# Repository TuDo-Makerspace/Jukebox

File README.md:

# Jukebox

This repository contains everything related to our sacred Jukebox. For more information, please refer to one of the following sections:

- [Usage](https://tudo-makerspace.github.io/Jukebox/Docs/Usage.html)
- [Hardware Documentation](https://tudo-makerspace.github.io/Jukebox/Docs/Hardware.html)
- [Software Documentation]() TODO

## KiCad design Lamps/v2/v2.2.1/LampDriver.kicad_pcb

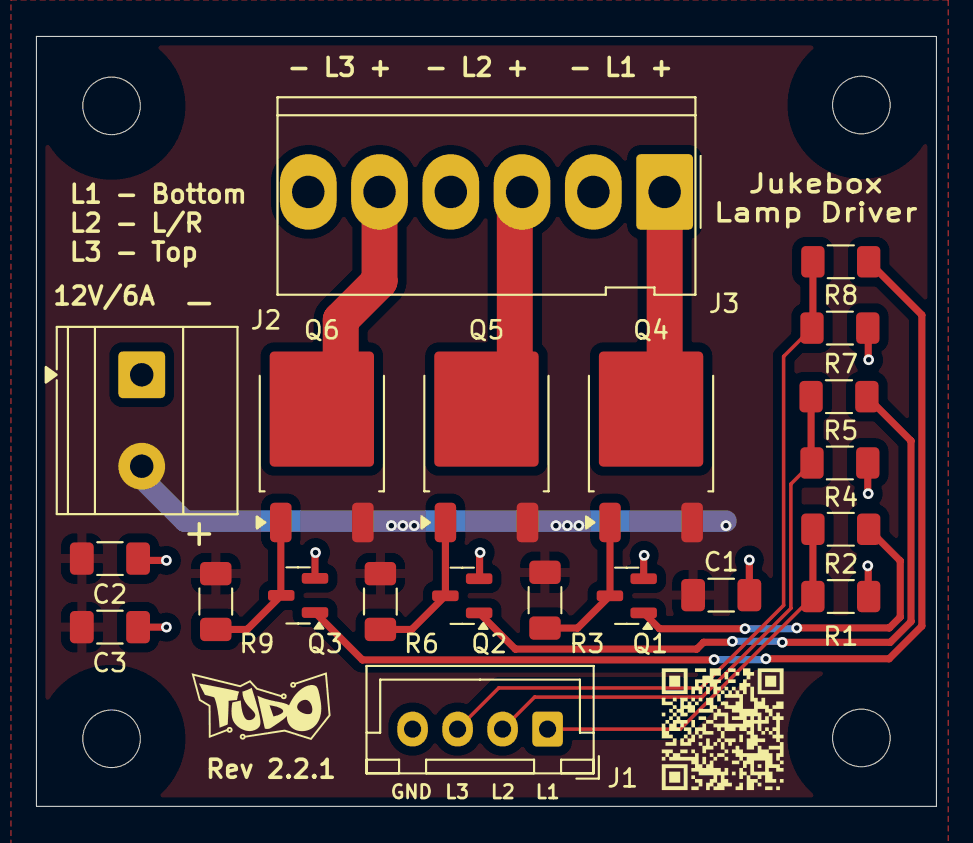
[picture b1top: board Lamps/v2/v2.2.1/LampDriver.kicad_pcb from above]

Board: 2 copper layers, 50.0 x 42.8 mm, 25 parts (0 on the bottom side), 14 nets.

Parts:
C1, C2: 100n; C_1206_3216Metric_Pad1.33x1.80mm_HandSolder
C3: 4.7u; C_1206_3216Metric_Pad1.33x1.80mm_HandSolder
H1, H2, H3, H4: MountingHole; MountingHole_3.2mm_M3
J1: JST XH 1x4; JST_XH_B4B-XH-A_1x04_P2.50mm_Vertical
J2: Screw_Terminal_01x02; TerminalBlock_Phoenix_MKDS-1,5-2-5.08_1x02_P5.08mm_Horizont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
J3: 1x6 MOLEX KK 396; Molex_KK-396_5273-06A_1x06_P3.96mm_Vertical
Q1, Q2, Q3: BSS138; SOT-23
Q4, Q5, Q6: FDD4141; TO-252-2
R1, R4, R7: 100k; R_1206_3216Metric_Pad1.30x1.75mm_HandSolder
R2, R5, R8: 470; R_1206_3216Metric_Pad1.30x1.75mm_HandSolder
R3, R6, R9: 47k; R_1206_3216Metric_Pad1.30x1.75mm_HandSolder

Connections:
+12V: C1.1, C2.1, C3.1, J2.2, Q4.3 (S), Q5.3 (S), Q6.3 (S), R3.1, R6.1, R9.1
/L1+: J3.1, Q4.2 (D)
/L2+: J3.3, Q5.2 (D)
/L3+: J3.5, Q6.2 (D)
GND: C1.2, C2.2, C3.2, J1.4, J2.1, J3.2, J3.4, J3.6, Q1.2 (S), Q2.2 (S), Q3.2 (S), R1.2, R4.2, R7.2
unnamed: J1.1, R1.1, R2.2
unnamed: J1.2, R4.1, R5.2
unnamed: J1.3, R7.1, R8.2
unnamed: Q1.3 (D), Q4.1 (G), R3.2
unnamed: Q1.1 (G), R2.1
unnamed: Q2.3 (D), Q5.1 (G), R6.2
unnamed: Q2.1 (G), R5.1
unnamed: Q3.3 (D), Q6.1 (G), R9.2
unnamed: Q3.1 (G), R8.1

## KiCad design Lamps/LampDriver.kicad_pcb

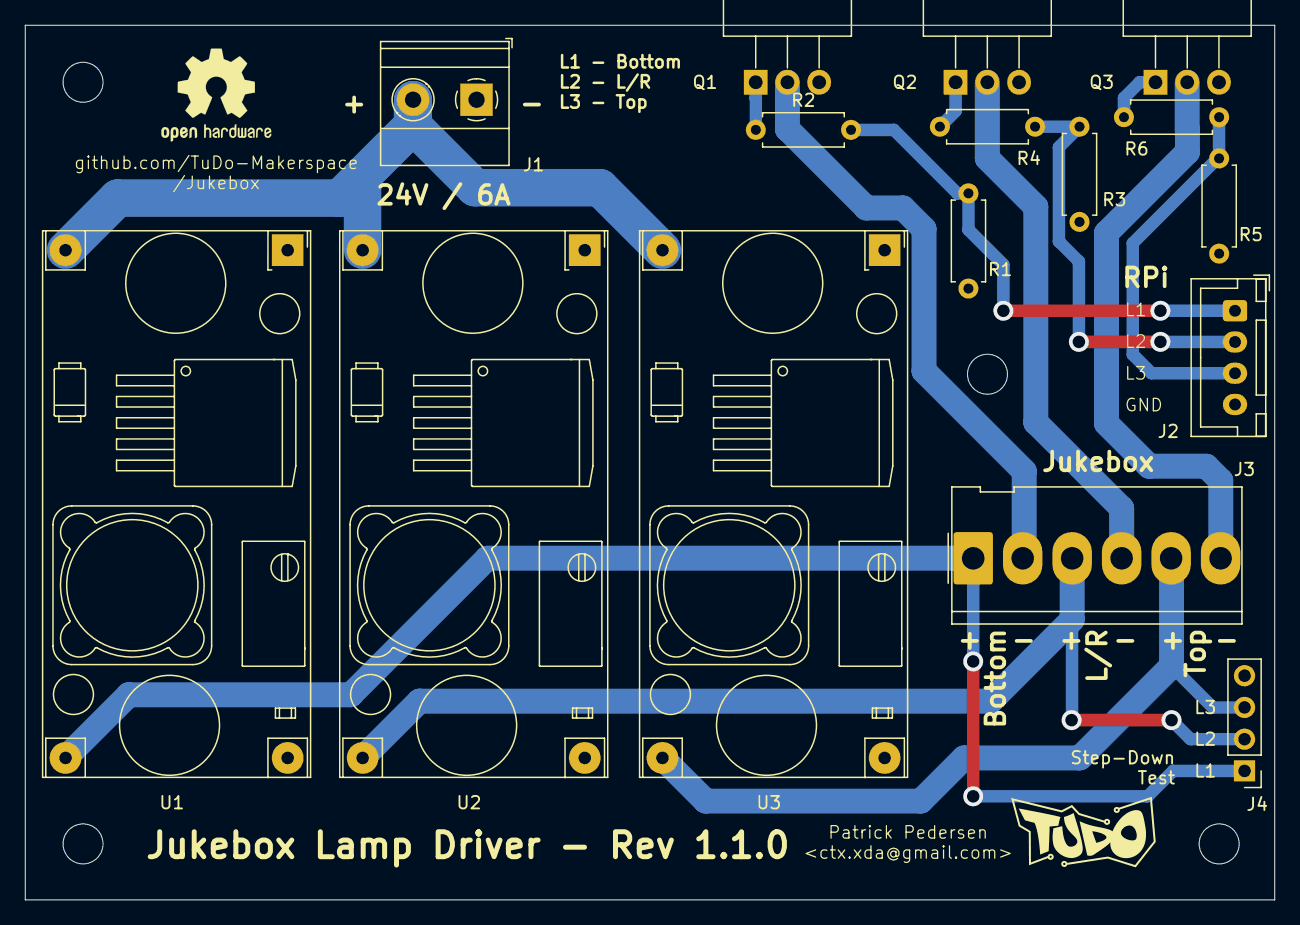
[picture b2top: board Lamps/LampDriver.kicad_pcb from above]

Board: 2 copper layers, 100.0 x 70.0 mm, 20 parts (0 on the bottom side), 14 nets.

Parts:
H1, H2, H3, H4: MountingHole; MountingHole_3.2mm_M3
J1: Screw_Terminal_01x02; TerminalBlock_Phoenix_MKDS-1,5-2-5.08_1x02_P5.08mm_Horizont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
J2: JST XH 1x4; JST_XH_B4B-XH-A_1x04_P2.50mm_Vertical
J3: Conn_01x06; Molex_KK-396_5273-06A_1x06_P3.96mm_Vertical
J4: Conn_01x04; PinHeader_1x04_P2.54mm_Vertical
Q1, Q2, Q3: IRFZ44N; TO-220-3_Horizontal_TabDown
R1, R3, R5: 100k; R_Axial_DIN0207_L6.3mm_D2.5mm_P7.62mm_Horizontal
R2, R4, R6: 470; R_Axial_DIN0207_L6.3mm_D2.5mm_P7.62mm_Horizontal
U1, U2, U3: DCDC_StepDown_LM2596; YAAJ_DCDC_StepDown_LM2596_Foxed

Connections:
+24V: J1.2, U1.1 (Vin), U2.1 (Vin), U3.1 (Vin)
/L1+: J3.1, J4.1, U1.4 (Vout)
/L1-: J3.2, Q1.2 (D)
/L2+: J3.3, J4.2, U2.4 (Vout)
/L2-: J3.4, Q2.2 (D)
/L3+: J3.5, J4.3, U3.4 (Vout)
/L3-: J3.6, Q3.2 (D)
GND: J1.1, J2.4, J4.4, Q1.3 (S), Q2.3 (S), Q3.3 (S), R1.2, R3.2, R5.2, U1.2 (GND), U1.3 (GND), U2.2 (GND), U2.3 (GND), U3.2 (GND), U3.3 (GND)
unnamed: J2.1, R1.1, R2.2
unnamed: J2.2, R3.1, R4.2
unnamed: J2.3, R5.1, R6.2
unnamed: Q1.1 (G), R2.1
unnamed: Q2.1 (G), R4.1
unnamed: Q3.1 (G), R6.1

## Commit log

2024-10-16 Added Lamp driver board
2024-10-16 Added adapter for speakers
2024-11-09 Added jukebox.py
2024-11-09 Added crude webserver to upload songs
2024-11-09 jukebox.py: Added play param to test playing
2024-11-09 Jukebox Webserver: Better upload errors + Fixed search bar
2024-11-10 Webserver: Added YouTube link support
2024-11-10 Webserver: Added spotify support
2024-11-10 Webserver: Expanded yt-dlp to more than just youtube links
2024-11-10 Webserver: Fixed upload buttons on phones
2024-11-10 Webserver: Added option to delte songs
2024-11-10 Webserver: Fixed uploads + BPM Tag after upload to reduce workload on jukebox.py
2024-11-10 Webserver: Added dark mode
2024-11-12 Renamed RPi/ to Software/
2024-11-12 Webserver: Run on port 80
2024-11-12 Software Setup: Added warning regarding missing assets
2024-11-12 Software Setup: Wait for services to activate
2024-11-12 Setup: Drop service check
2024-11-12 Jukebox: Keypad LUT
2024-11-12 Jukebox: Keypad mapping + Minor test arg fix
2024-11-12 Jukebox: Fixed keypad edgecase
2024-11-12 Jukebox: Added keypad timeout
2024-11-12 Webserver: Use env path!
2024-11-12 Removed accidental push of song
2024-11-12 Setup: Do not spam /etc/environment
2024-11-12 Jukebox: Play Track Not Found sample
2024-11-13 Jukebox: Added stop button + Other minor fixes
2024-11-13 Jukebox: Added boot light animation
2024-11-13 Jukebox: Added bpm multiplier to spice up the lights
2024-11-13 Jukebox: Added logs
2024-11-13 Jukebox: Dropped -p in favor of requiring JUKEBOX_SONGS_PATH
2024-11-14 Webserver: Outsource downloads to server if possible
2024-11-14 Webserver: Fixed white text on darkmode
2024-11-14 Setup: Add prompts for webserver env vars
2024-11-14 Webserver: Re-added -d
2024-11-14 Webserver: Fixed python formatting errors
2024-11-14 Fixed bad env vars
2024-11-14 Webserver: Added name feature + Better escaping
2024-11-14 Webserver: Added reminder to update title cards
2024-11-14 Webserver: Fixed Spotify Downloads
2024-11-14 Setup: Do not use -p in systemd service!
2024-11-14 Jukebox: Added support for random button
2024-11-14 Webserver: SSH: Disable StrictHostKeyChecking
2024-11-14 Jukebox: Fixed wrong compare on random button
2024-11-14 Webserver: Sanitize names because of @MarcelLeonMrgic :)
2024-11-14 Webserver: Break on characters in trackname
2024-11-14 Webserver: Limit track title in upload modal
2024-11-15 Jukebox: Implemented idle mode
2024-11-15 Jukebox: Minor fixes to idle mode
2024-11-15 Jukebox: More idle fixes
2024-11-15 Webserver: Allow 0-999
2024-11-15 Webserver: Fixed off-by-one error
2024-11-15 Jukebox: Added soundboard support
2024-11-16 Jukebox: Added soundboard
2024-11-16 Jukebox: Added function to set all lights
2024-11-16 Jukebox: Added timeout for soundboard mode
2024-11-16 Webserver: Added site for soundboard
2024-11-16 Webserver: Seperated css + Listen for ENTER in search bar
2024-11-17 Jukebox: Support soumdboard samples for non-numeric keys
2024-11-17 Webserver: Soundboard: Added support for R, G, RED and BLUE keys
2024-11-17 Jukebox: Soundboard: Added missing sample sound + Preload samples whenever we enter soundboard
2024-11-17 Webserver: Show reminder to re-enter soundboard after updating it
2024-11-17 Jukebox: If no command provided, show help
2024-11-17 Jukebox: Preload all assets to faster responsiveness
2024-11-18 Webserver: Show blue and red circle emojis for blue and red button in sb
2024-11-18 Jukebox: Sampling rate weirdness
2024-11-18 Jukebox: Sample buttons for better reliability + Fixed soundboard
2024-11-18 Jukebox: Renamed TrackNotFound.wav to TrackMissing.wav
2024-11-18 Added gitignore
2024-11-18 Jukebox: Soundboard: Play sample on button press, not release
2024-11-20 Webserver: See commit details
    Samples:
    - Fixed deletions of samples
    - Convert non 44100 or 48000 wavs to 44100
    As well as minor code clean-up
2024-11-20 Jukebox: Minor fixes
2024-11-20 Jukebox: Refactored key releasing
2024-11-20 Jukebox: More minor key release improvements
2025-02-24 Lamps: Rev 2.0 of lamp driver board
2025-03-22 Jukebox: Implement sample banks
2025-03-22 Jukebox: New lights board uses active high logic
2025-03-28 Webserver: Add sample bank pages
2025-03-28 Webserver: Fix delete and upload for banks
2025-03-28 Templates: Call new endpoints
2025-03-28 Jukebox: Always enter soundboard with bank 0
2025-03-28 Jukebox: Return if key not found for sample
2025-03-28 Jukebox: Seperate assets and samples
2025-03-28 Jukebox: Added press sound
2025-03-28 Webserver: Do not use red and blue keys for samples
2025-03-28 Webserver: Fix akward arrow buttons on dark mode
2025-03-28 Jukebox: Play press sound even when exiting idle mode
2025-03-28 Webserver: Init bank_dir earlier
2025-03-28 jukebox: Play press asset in red, blue yellow in soundboard mode
2025-04-10 Jukebox: Improve press sound
2025-04-10 Webserver: Trim silence at start of samples
2025-04-10 Webserver: Refactored sox trimming to function
2025-04-10 Docs: Add usage guide
2025-04-10 Docs: Added html version of Usage.md
2025-04-10 Added crude readme
2025-04-11 Docs: Update Usage and drop markdown version
2025-04-11 README: Refer to usage html
2025-04-11 Flowchart: Minor correction
2025-04-11 Docs: Improve flowchart
2025-04-11 Jukebox: Shuffle until abort
2025-04-12 Jukebox: Minor change
2025-04-12 Docs: Document new shuffle feature
2025-04-12 jukebox_webserver: Perform lufs normalization on uploaded tracks and samples
2025-04-13 First draft of hardware docs
2025-04-13 Docs: Added speaker info
2025-04-13 Keypad: Add kicad schematic
2025-04-13 Docs: Add info on amps
2025-04-13 Docs: Minor change
2025-04-15 Keypad: Kicad schematic completed
2025-04-15 Docs: More keypad stuff
2025-04-16 Docs: Hardware: Added photo of electronics
2025-04-16 Docs: Hardware: Make images clickable
2025-04-16 README: Add link to hardware docs
2025-04-16 Docs: Hardware: Minor correction
2025-04-16 Sound: Add DSP file
2025-04-17 Docs: Hardware: Add info about clear button gpio
2025-04-17 Docs: Hardware: Minor correction in Keypad table
2025-04-17 Webserver: Try to do normalization on server
2025-04-30 Webserver: See description
    - Better file name handling
    - Specify exact ffmpeg location
    - Minor logging improvements
2025-05-01 Jukebox Webserver: Perform LUFS norm on ytdl and spotdl
2025-11-06 Lamps: PCB rev 2.2.0
2025-11-08 Lamps: PCB: Last touches
2025-11-08 Lamps: PCB: minor changes qualify as v2.2.1
2025-11-25 Docs: Update Lamp driver docs
